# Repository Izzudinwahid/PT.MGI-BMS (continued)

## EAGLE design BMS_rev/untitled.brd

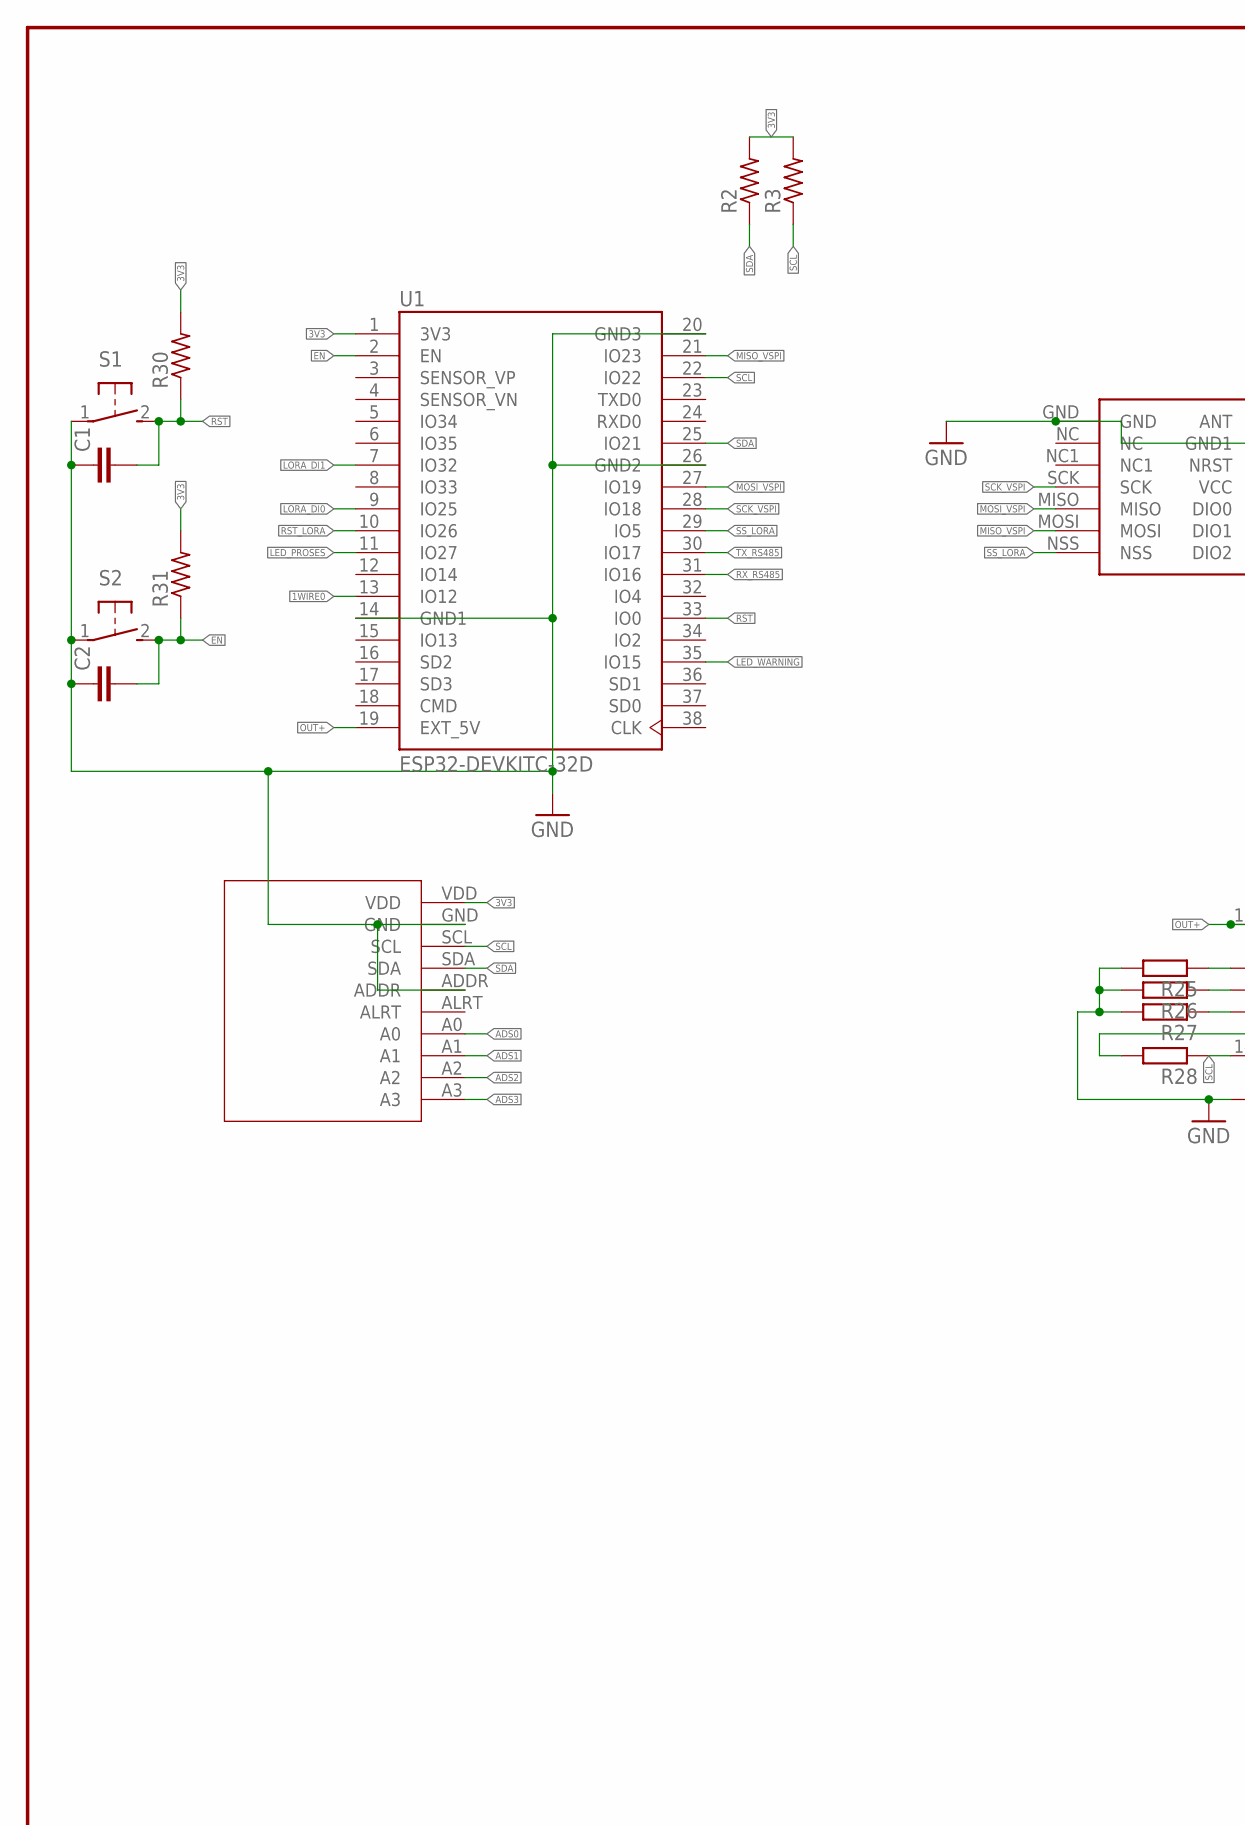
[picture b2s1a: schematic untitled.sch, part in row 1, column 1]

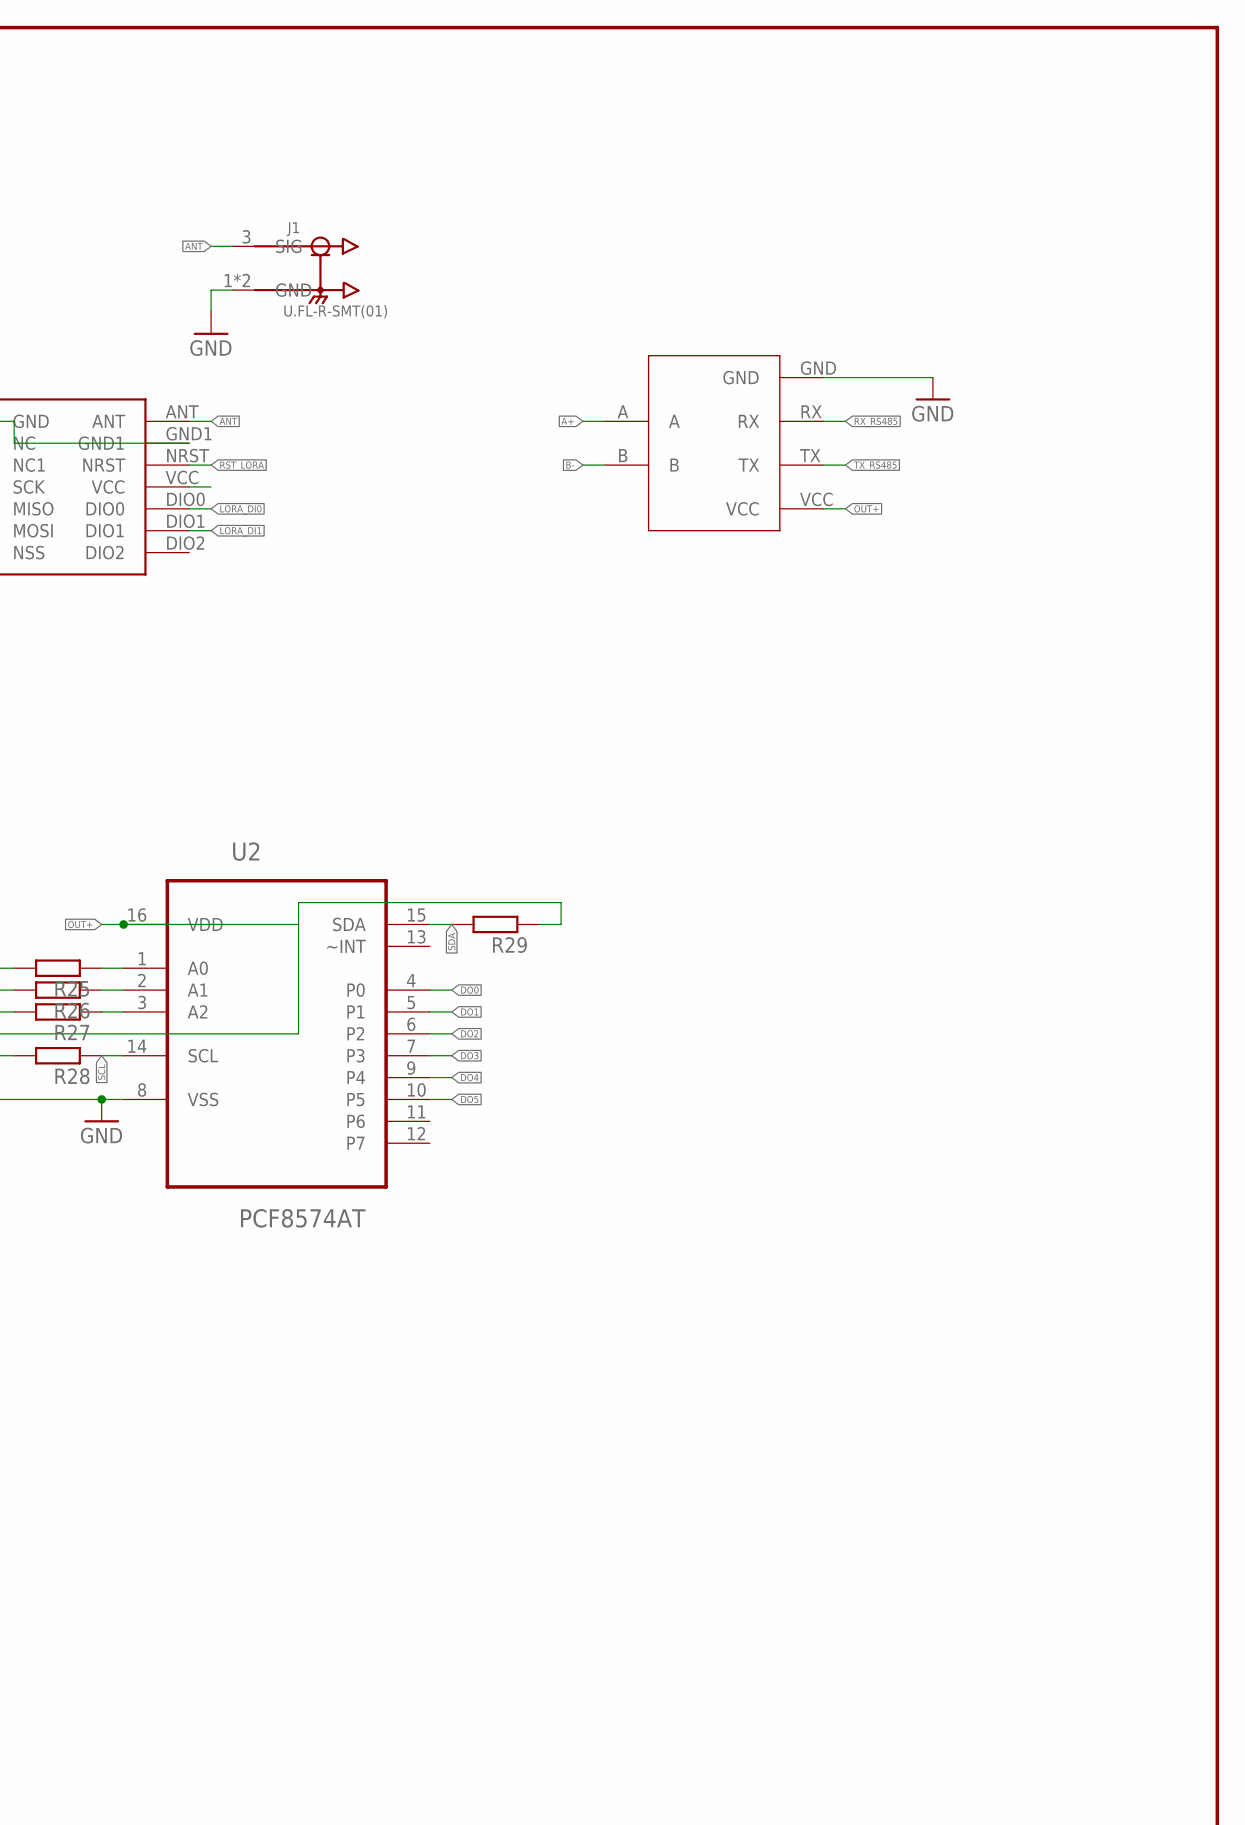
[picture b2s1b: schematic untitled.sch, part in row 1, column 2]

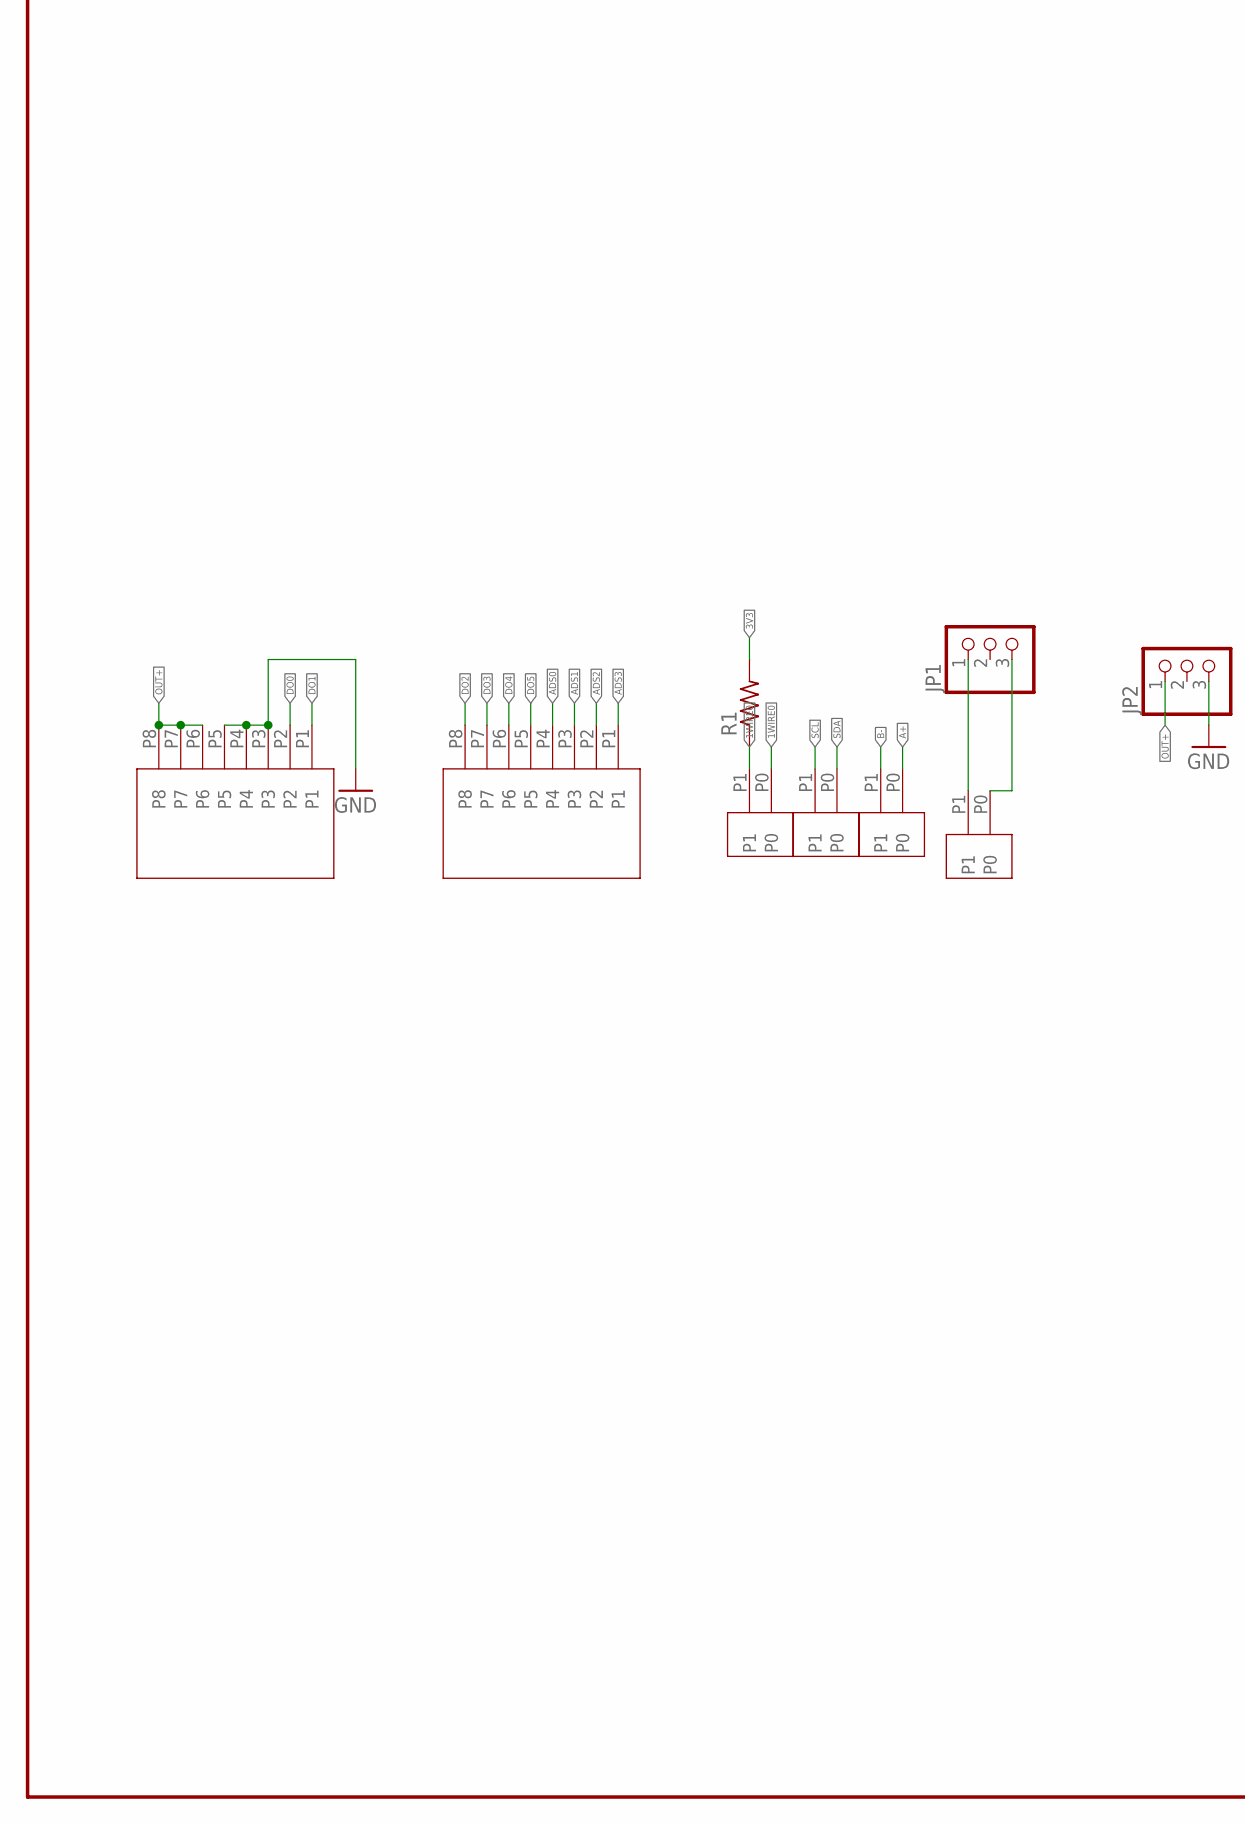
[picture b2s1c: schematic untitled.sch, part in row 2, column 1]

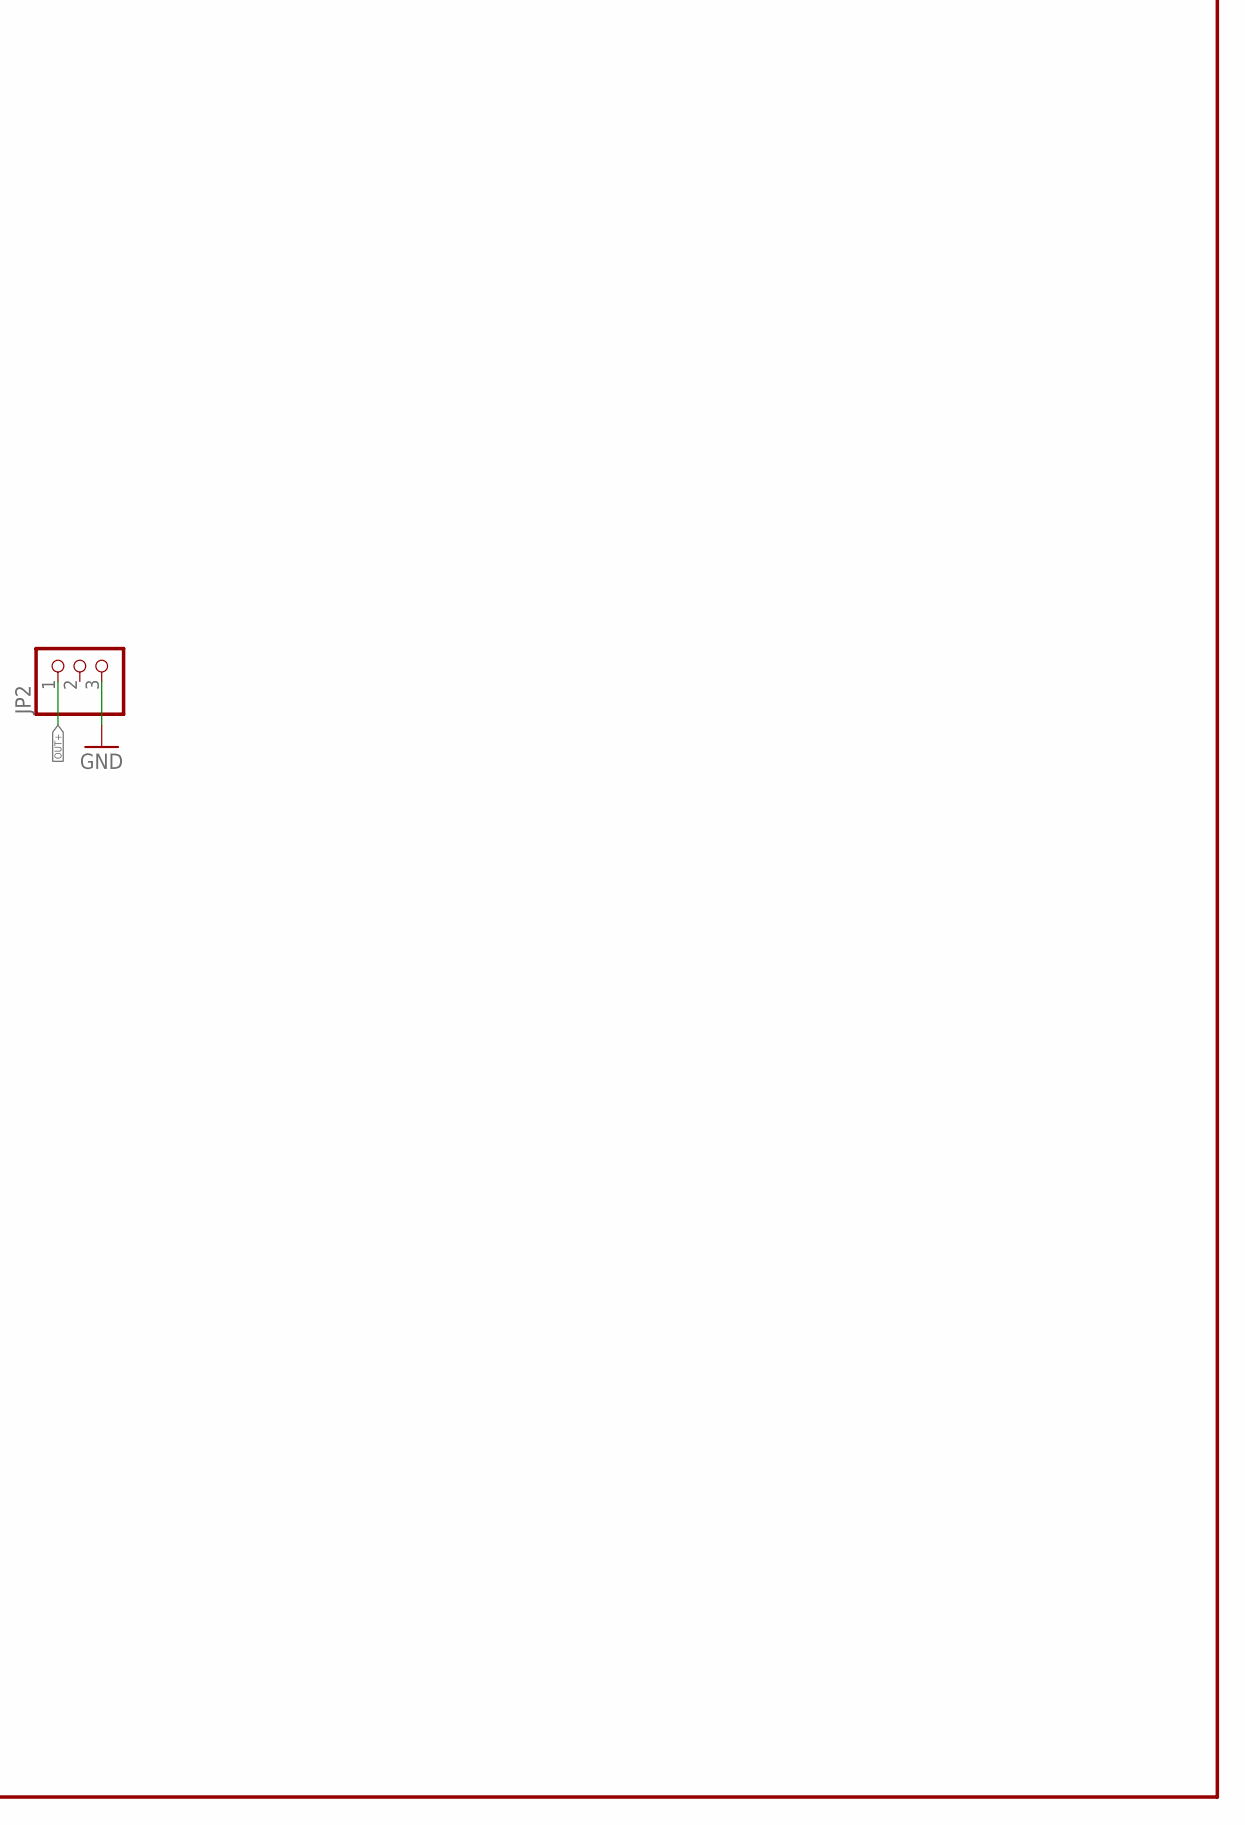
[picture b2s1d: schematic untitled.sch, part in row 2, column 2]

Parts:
ADS1: ADS1115
C1, C2: C-EUC0805K; C0805K
CONN2P-3.5PI1, CONN2P-3.5PI2, CONN2P-3.5PI3, CONN2P-3.5PI5: CONN2P-3.5PI
CONN3.1, CONN3.2: CONN3.5
J1: U.FL-R-SMT(01); HRS_U.FL-R-SMT(01)
JP1, JP2: PINHD-1X3; 1X03
LORA-NICERF-V1: LORA-NICERF-V2
R1, R2, R3, R30, R31: R-US_M0805; M0805
R25, R26, R27, R28, R29: R-EU_R0805; R0805
S1, S2: 31-XX; B3F-31XX
TTL-RS1: TTL-RS485
U1: ESP32-DEVKITC-32D; MODULE_ESP32-DEVKITC-32D
U2: PCF8574AT; SOIC127P1032X265-16N

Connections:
1WIRE0: CONN2P-3.5PI3.P0, CONN2P-3.5PI3.P1, R1.1, U1.13 (IO12)
3V3: ADS1.VDD, R1.2, R2.2, R3.2, R30.2, R31.2, U1.1 (3V3)
A+: CONN2P-3.5PI5.P0, TTL-RS1.A
ADS0: ADS1.A0, CONN3.2.P4
ADS1: ADS1.A1, CONN3.2.P3
ADS2: ADS1.A2, CONN3.2.P2
ADS3: ADS1.A3, CONN3.2.P1
ANT: J1.3 (SIG), LORA-NICERF-V1.ANT
B-: CONN2P-3.5PI5.P1, TTL-RS1.B
DO0: CONN3.1.P2, U2.4 (P0)
DO1: CONN3.1.P1, U2.5 (P1)
DO2: CONN3.2.P8, U2.6 (P2)
DO3: CONN3.2.P7, U2.7 (P3)
DO4: CONN3.2.P6, U2.9 (P4)
DO5: CONN3.2.P5, U2.10 (P5)
EN: C2.2, R31.1, S2.2 (S), U1.2 (EN)
GND: ADS1.ADDR, ADS1.GND, C1.1, C2.1, CONN3.1.P3, CONN3.1.P4, CONN3.1.P5, J1.1 (GND), J1.2 (GND), JP2.3, LORA-NICERF-V1.GND, LORA-NICERF-V1.GND1, R25.2, R26.2, R27.2, S1.1, S2.1, TTL-RS1.GND, U1.14 (GND1), U1.20 (GND3), U1.26 (GND2), U2.8 (VSS)
LED_PROSES: U1.11 (IO27)
LED_WARNING: U1.35 (IO15)
LORA_DI0: LORA-NICERF-V1.DIO0, U1.9 (IO25)
LORA_DI1: LORA-NICERF-V1.DIO1, U1.7 (IO32)
MISO_VSPI: LORA-NICERF-V1.MOSI, U1.21 (IO23)
MOSI_VSPI: LORA-NICERF-V1.MISO, U1.27 (IO19)
unnamed: R25.1, U2.1 (A0)
unnamed: R26.1, U2.2 (A1)
unnamed: R27.1, U2.3 (A2)
unnamed: CONN2P-3.5PI1.P1, JP1.1
unnamed: CONN2P-3.5PI1.P0, JP1.3
OUT+: CONN3.1.P6, CONN3.1.P7, CONN3.1.P8, JP2.1, R28.2, R29.1, TTL-RS1.VCC, U1.19 (EXT_5V), U2.16 (VDD)
RST: C1.2, R30.1, S1.2 (S), U1.33 (IO0)
RST_LORA: LORA-NICERF-V1.NRST, U1.10 (IO26)
RX_RS485: TTL-RS1.RX, U1.31 (IO16)
SCK_VSPI: LORA-NICERF-V1.SCK, U1.28 (IO18)
SCL: ADS1.SCL, CONN2P-3.5PI2.P1, R3.1, R28.1, U1.22 (IO22), U2.14 (SCL)
SDA: ADS1.SDA, CONN2P-3.5PI2.P0, R2.1, R29.2, U1.25 (IO21), U2.15 (SDA)
SS_LORA: LORA-NICERF-V1.NSS, U1.29 (IO5)
TX_RS485: TTL-RS1.TX, U1.30 (IO17)

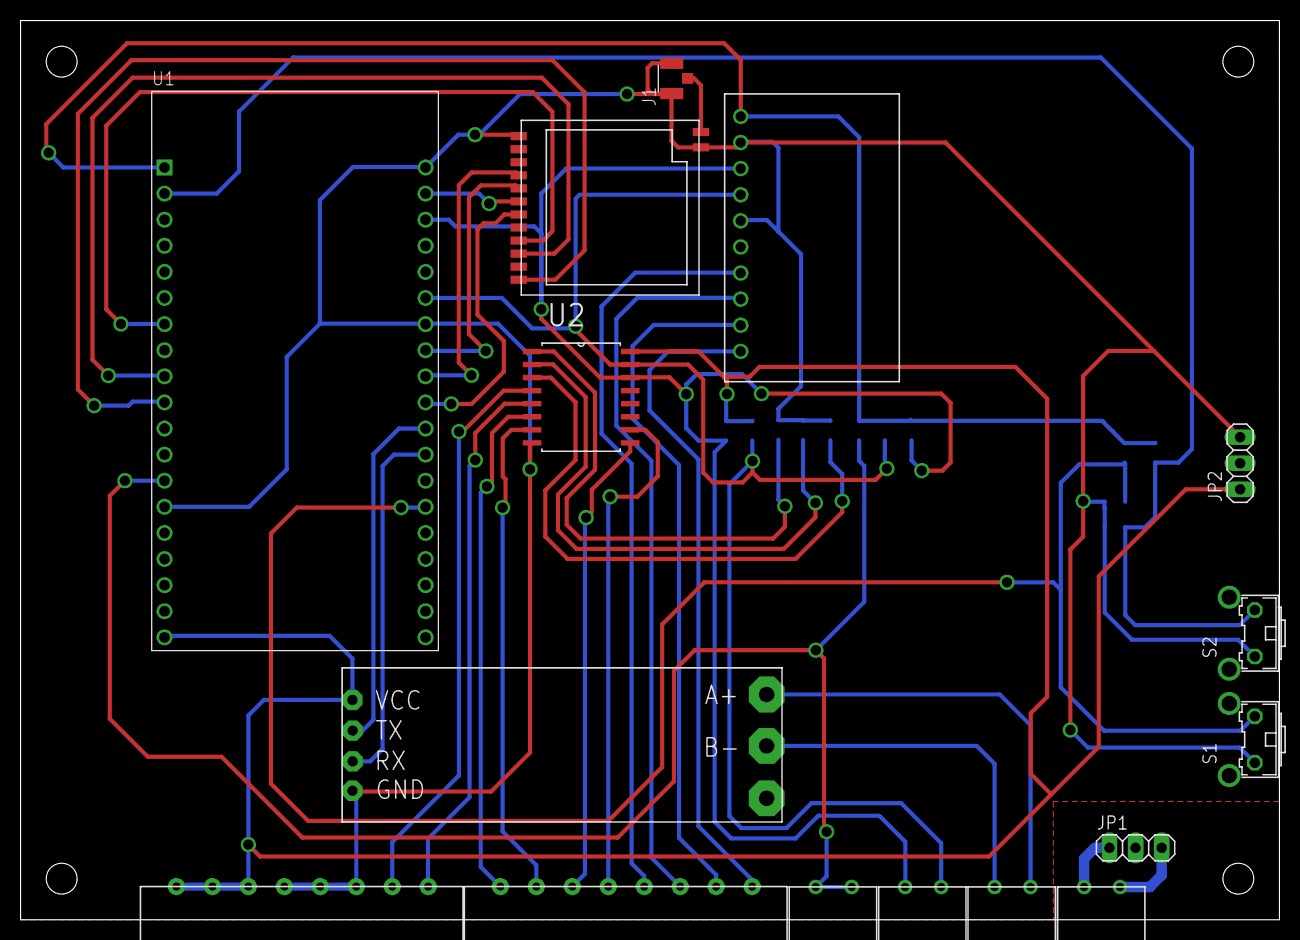
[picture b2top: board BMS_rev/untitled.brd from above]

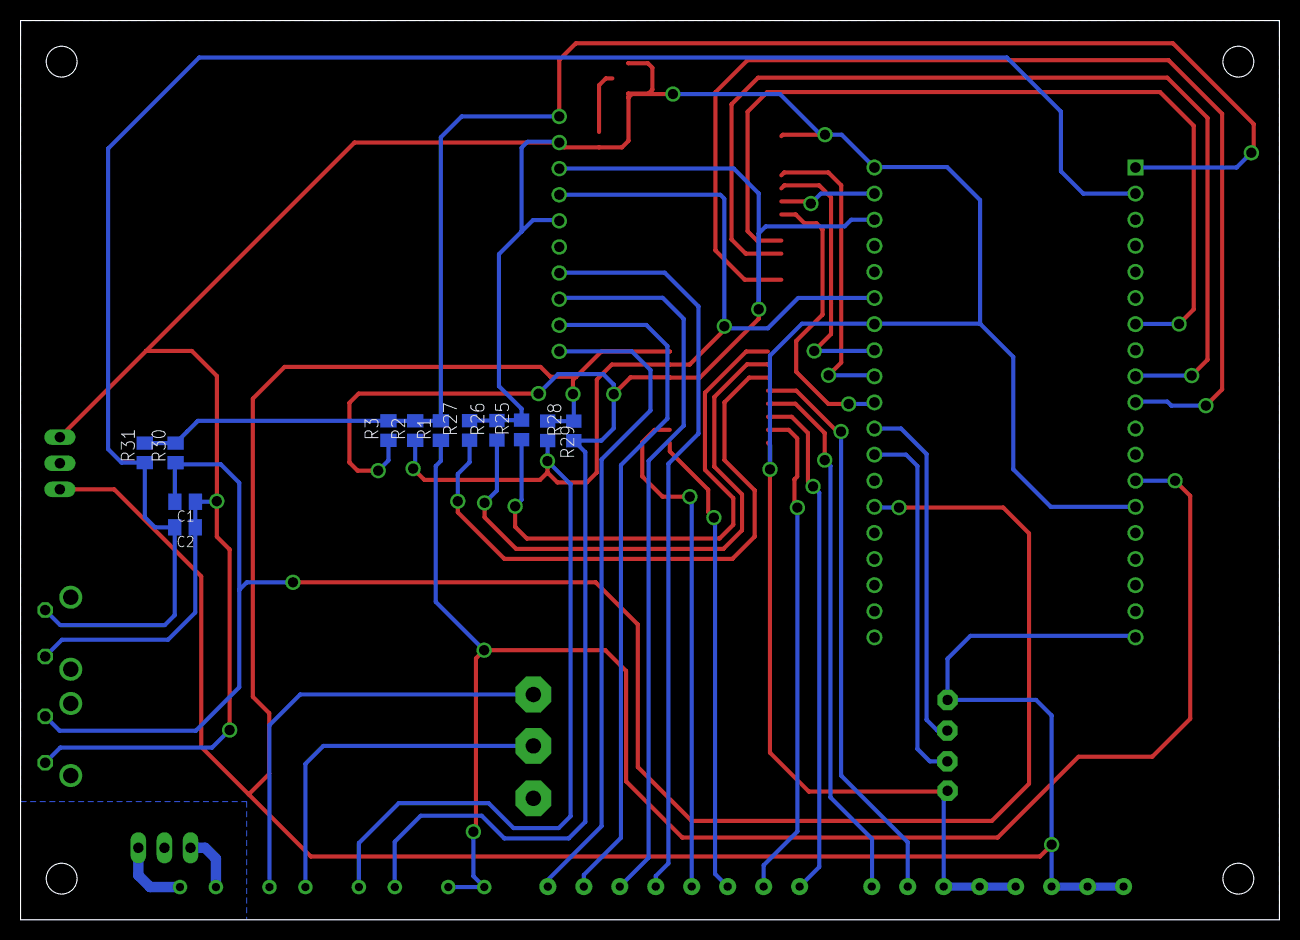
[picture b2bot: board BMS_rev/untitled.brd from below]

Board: 2 copper layers, 122.5 x 87.5 mm, 28 parts (12 on the bottom side), 35 nets.

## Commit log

2022-11-21 rangkaian schematic BMS
2022-12-02 revisi PCB
2022-12-02 menambahkan pullup i2c
2023-04-17 PCB BMS
2023-06-06 PCB BMSv1.1
2023-06-20 fix PCB v1.0
2024-08-05 PCB BMS v1.2
